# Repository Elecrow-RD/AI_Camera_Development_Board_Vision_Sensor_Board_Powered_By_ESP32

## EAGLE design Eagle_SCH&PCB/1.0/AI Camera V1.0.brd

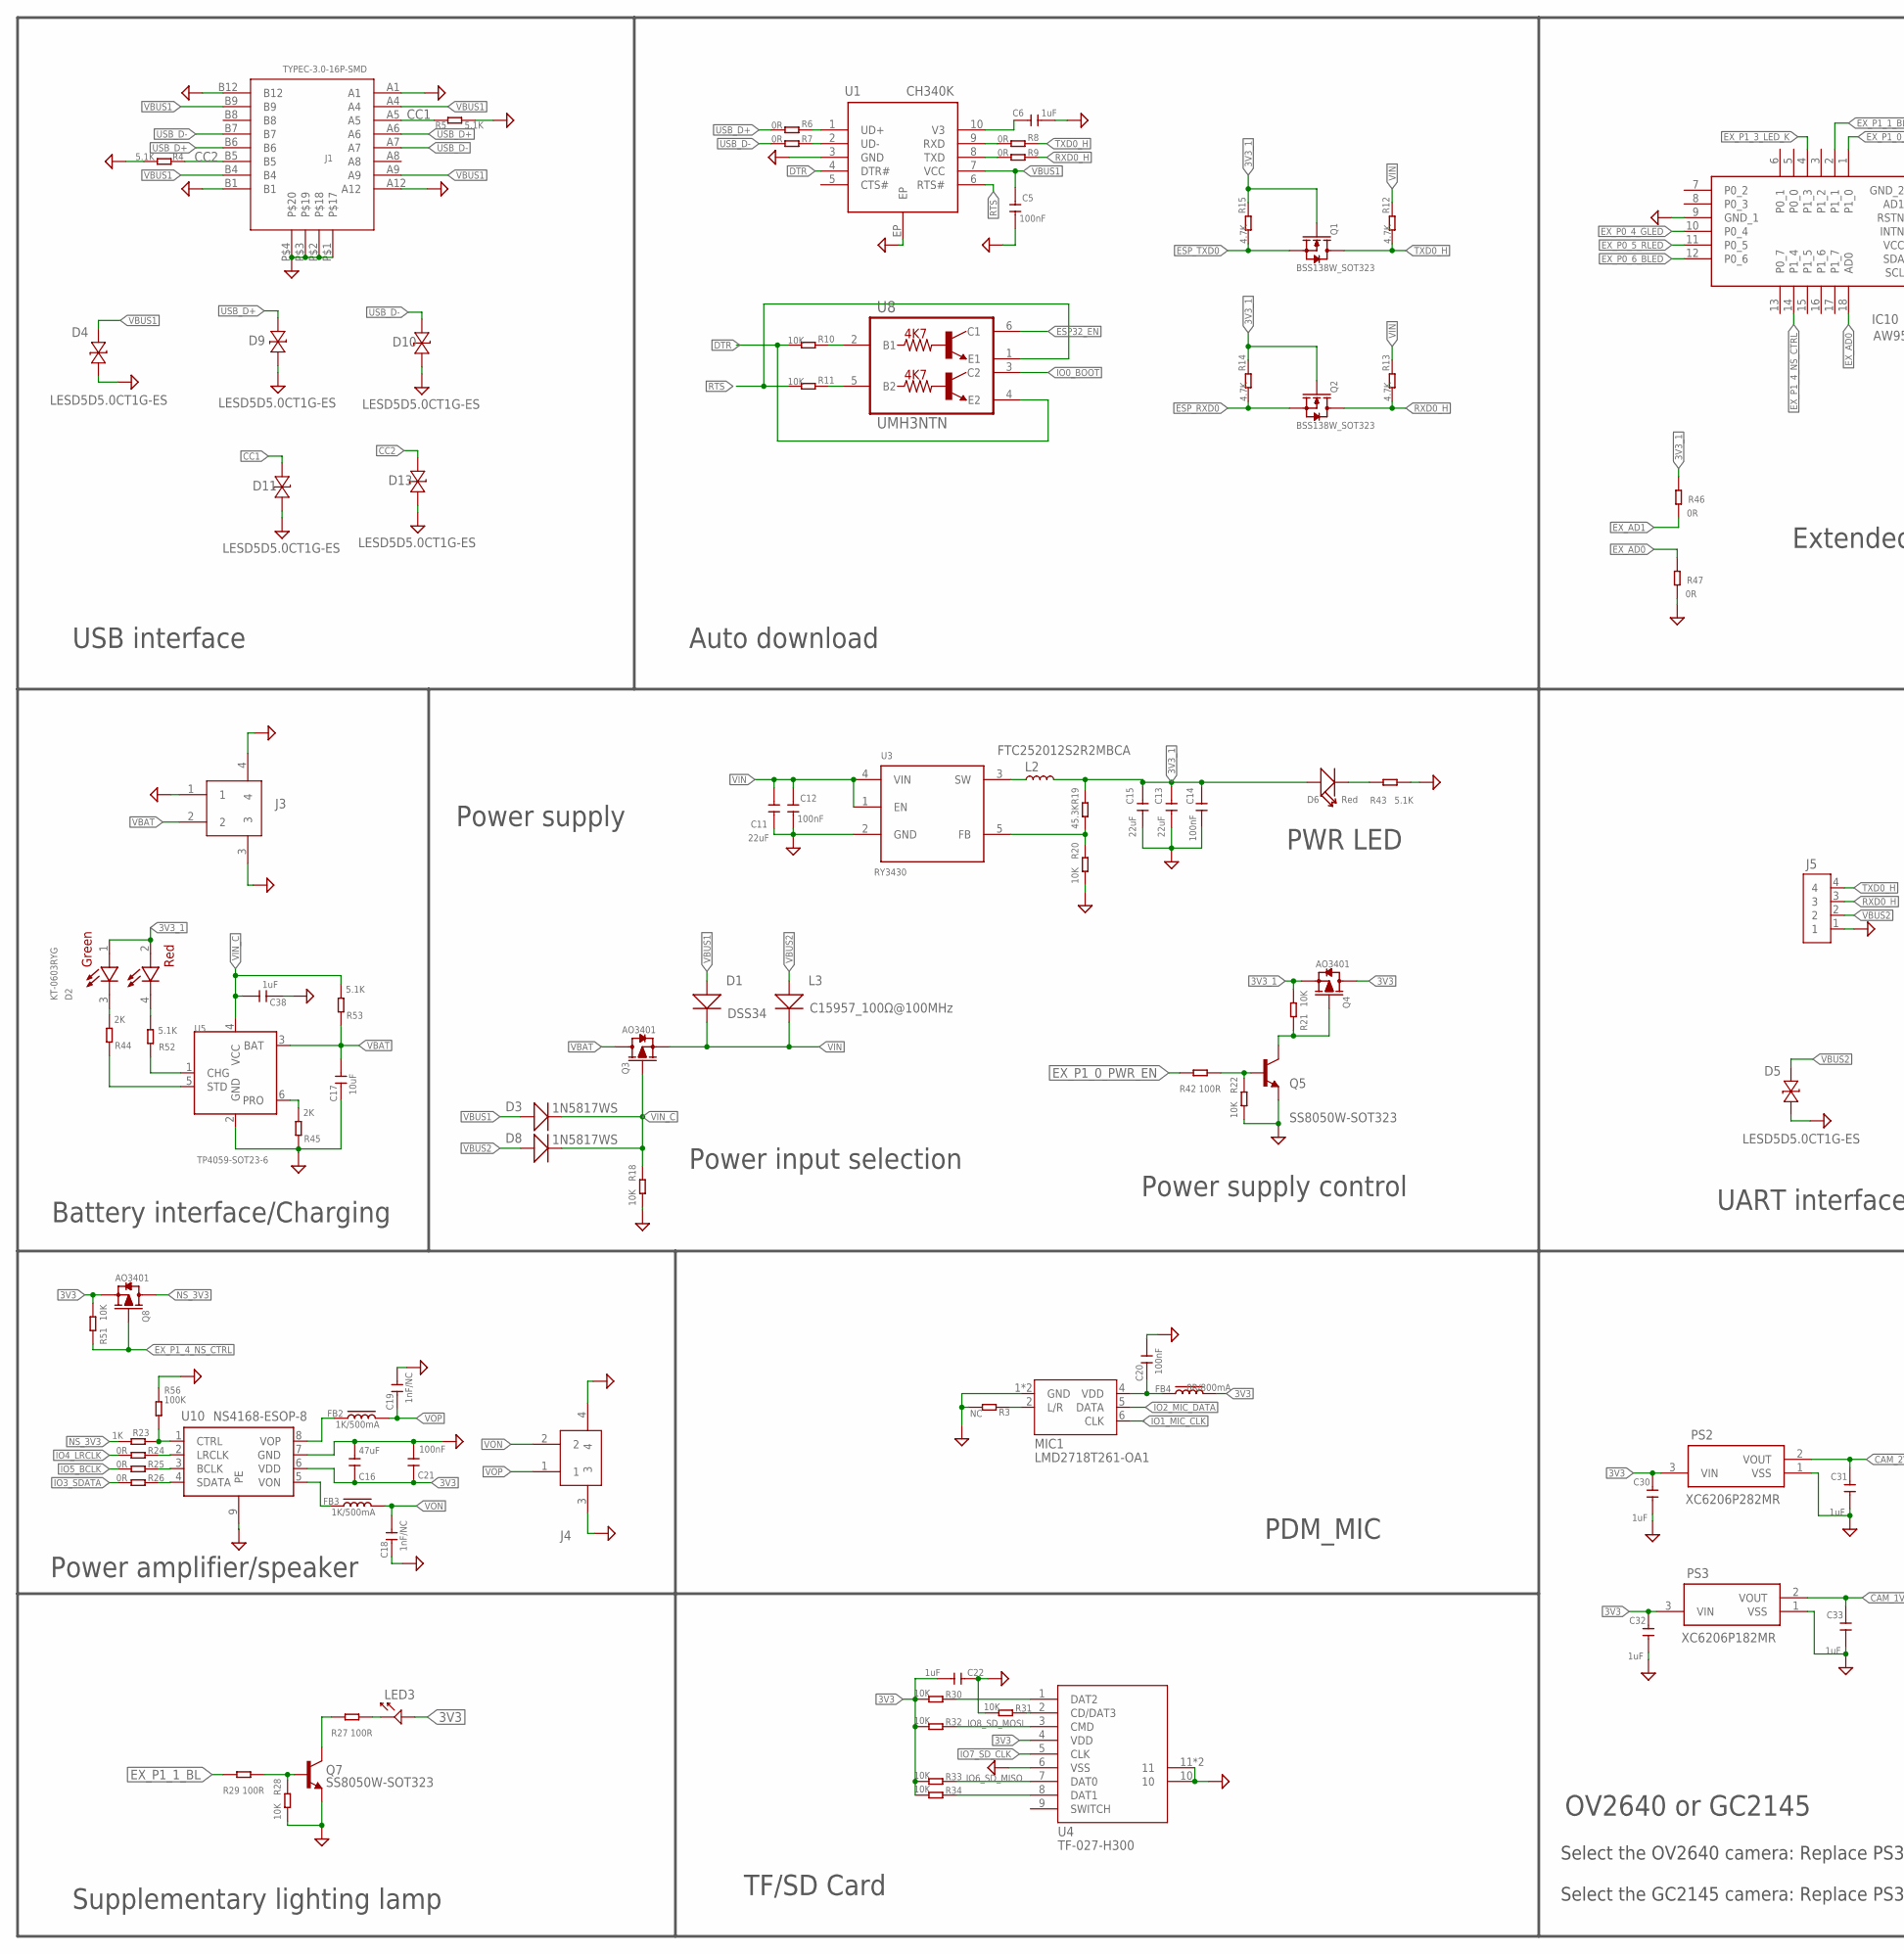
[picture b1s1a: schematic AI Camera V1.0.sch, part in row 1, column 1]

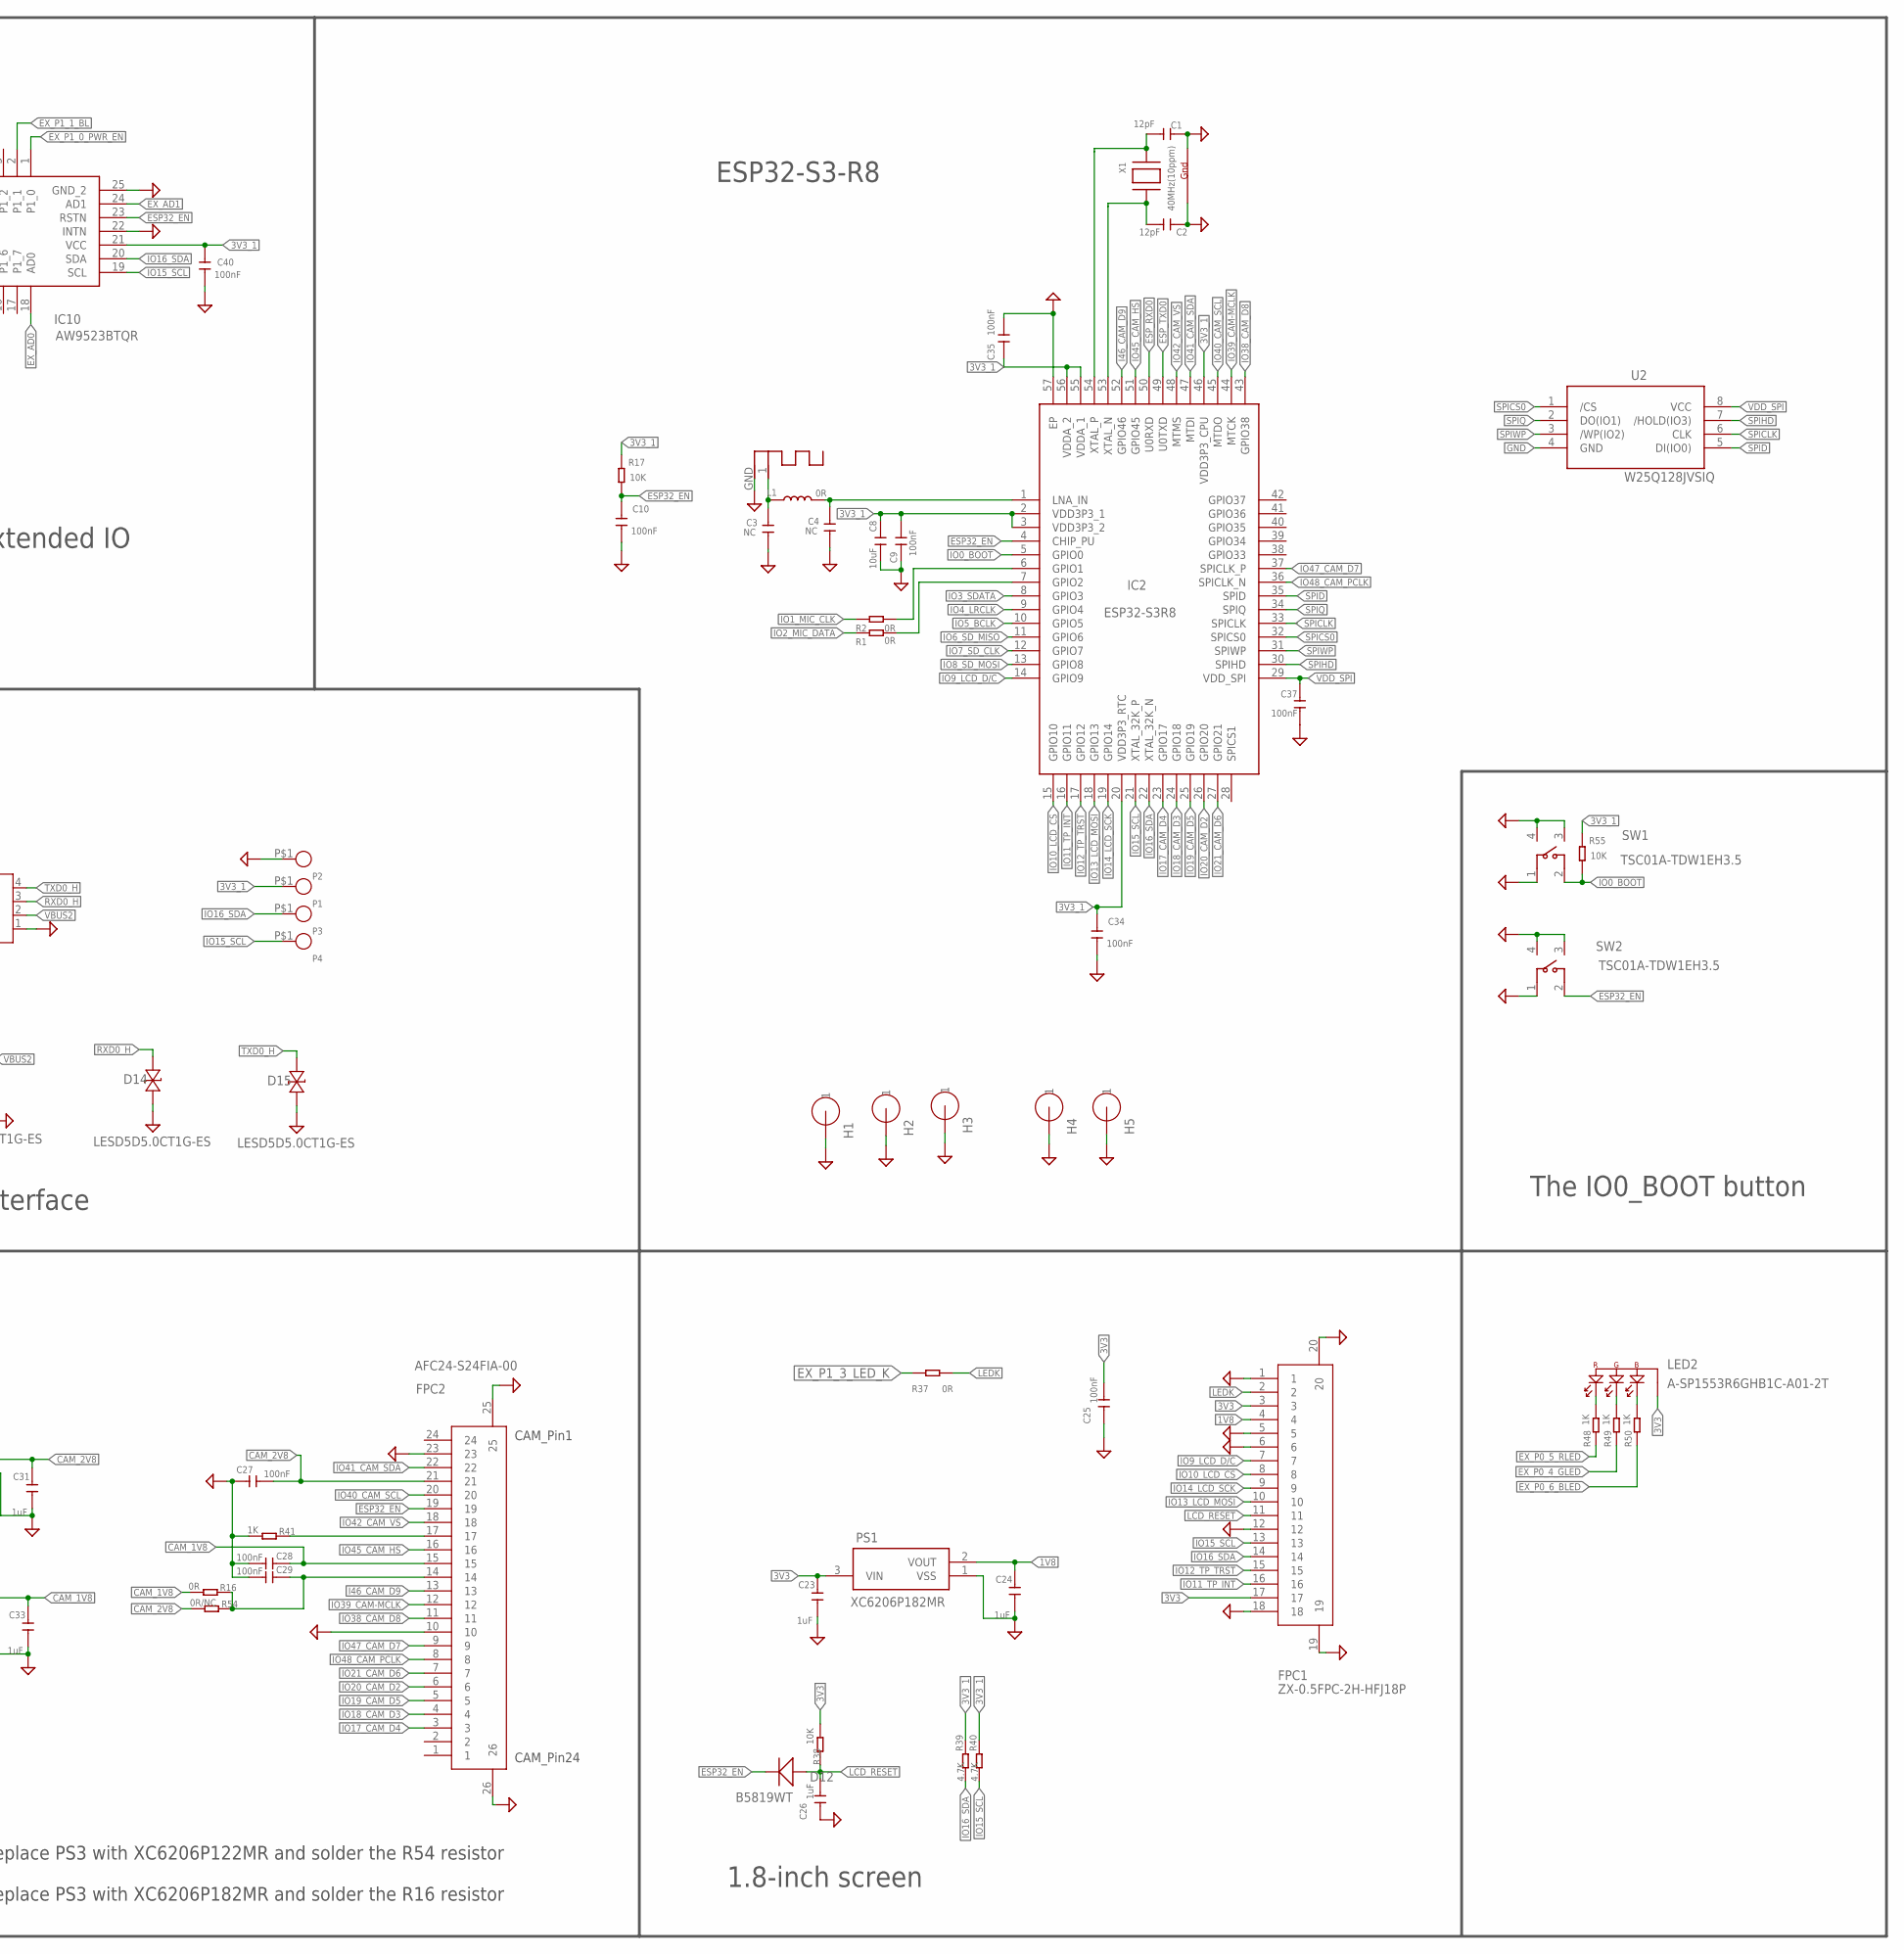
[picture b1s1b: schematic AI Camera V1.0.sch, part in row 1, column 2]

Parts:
ANT1: ADAFRUIT_ANTENNA; ADAFRUIT_RN-ANT
C1, C2: 12pF; C0402
C3, C4: NC; C0402
C5, C9, C10, C12, C14, C20, C21, C25, C27, C28, C29, C34, C35, C37, C40: 100nF; C0402
C6, C22, C23, C24, C26, C30, C31, C32, C33, C38: 1uF; C0402
C8, C17: 10uF; C0402
C11, C13, C15: 22uF; C0603
C16: 47uF; C0805
C18, C19: 1nF/NC; C0402
D1: DSS34; D_SOD123FL
D2: KT-0603RYG; LED_KT-0603RYG
D3, D8: 1N5817WS; D_SOD323
D4, D5, D9, D10, D11, D13, D14, D15: LESD5D5.0CT1G-ES; SOD-523_L1.2-W0.8-LS1.6-BI
D6: Red; LED0603
D12: B5819WT; D_SOD523
FB2, FB3: 1K/500mA; L0603
FB4: 0R/800mA; L0603
FPC1: ZX-0.5FPC-2H-HFJ18P; FPC-SMD_18P-P0.50_ZX-0.5FPC-2H-HFJ18P
FPC2: AFC24-S24FIA-00; FPC-SMD_P0.50-24P_QCHF-SM-H2.0
H1, H2, H3: HOLE; HOLE_M2
H4, H5: HOLE1; LONGSTRIPHOLE
IC2: ESP32-S3R8; QFN40P700X700X90-57N
IC10: AW9523BTQR; QFN50P400X400X80-25N
J1: TYPEC-3.0-16P-SMD; USB-3.0TYPEC-SMD
J3: ZX-SH1.0-2PLT1; CONN-SMD_2P-P1.00_XUNPU_WAFER-SH1.0-2PWB
J4: HC-1.25-2PWT; CONN-SMD_2P-P1.25-HC-1.25-2PWT
J5: HC-HY-4A-M; CONN-TH_4P-P2.00_HCTL_HC-HY-4A
L1: 0R; L0402
L2: FTC252012S2R2MBCA; IND-SMD_L2.5-W2.0_MHCHL2520
L3: C15957_100Ω@100MHz; D_SOD123FL
LED2: A-SP1553R6GHB1C-A01-2T; LED-SMD_4P-L3.2-W2.7-BL_A-SP1553R6GHB1C-A01-2T
LED3: 3014_LED; LED_3014_SMT
MIC1: LMD2718T261-OA1; MIC-SMD_6P-L2.8-W1.9-P0.98-TL
P1, P2, P3, P4: TEST_PADPAD-1.5MM; TEST_PAD-1.5MM
PS1, PS3: XC6206P182MR; SOT95P280X130-3N
PS2: XC6206P282MR; SOT95P280X130-3N
Q1, Q2: BSS138W_SOT323; MOS_SOT323
Q3, Q4, Q8: AO3401; PMOS_SOT23
Q5, Q7: SS8050W-SOT323; MOS_SOT323
R1, R2, R6, R7, R8, R9, R16, R24, R25, R26, R37, R46, R47: 0R; R0402
R3: NC; R0402
R4, R5, R43, R52, R53: 5.1K; R0402
R10, R11, R17, R18, R20, R21, R22, R28, R30, R31, R32, R33, R34, R38, R51, R55: 10K; R0402
R12, R13, R14, R15, R39, R40: 4.7K; R0402
R19: 45.3K; R0402
R23, R41, R48, R49, R50: 1K; R0402
R27, R29, R42: 100R; R0402
R44, R45: 2K; R0402
R54: 0R/NC; R0402
R56: 100K; R0402
SW1, SW2: TSC01A-TDW1EH3.5; KEY-SMD_4P-L4.6-W2.4_TSC01A-TDW1FH3.5
U1: CH340K; ESOP-10-EP-150MIL
U2: W25Q128JVSIQ; CKP_W25QXX-SOP-8-208MIL
U3: RY3430; IC_SOT23-5
U4: TF-027-H300; TF-SMD_HYCW104-TF08-375B
U5: TP4059-SOT23-6; SOT23-6L
U8: UMH3NTN; SOP65P210X100-6N
U10: NS4168-ESOP-8
X1: 40MHz(10ppm); ADAFRUIT_NX3225

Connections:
1V8: C24.1, FPC1.4, PS1.2 (VOUT)
3V3: C16.1, C21.1, C22.2, C23.1, C25.2, C30.1, C32.1, FB4.2, FPC1.3, FPC1.17, LED2.3 (GND), LED3.1, PS1.3 (VIN), PS2.3 (VIN), PS3.3 (VIN), Q4.3 (D), Q8.2 (S), R30.2, R32.2, R33.2, R34.2, R38.2, R51.2, U4.4 (VDD), U10.6 (VDD)
3V3_1: C8.1, C9.2, C13.2, C14.1, C15.2, C34.2, C35.1, C40.2, D2.1, D2.2, D6.+, IC2.2 (VDD3P3_1), IC2.3 (VDD3P3_2), IC2.20 (VDD3P3_RTC), IC2.46 (VDD3P3_CPU), IC2.55 (VDDA_1), IC2.56 (VDDA_2), IC10.21 (VCC), L2.2, P1.P$1, Q1.1 (G), Q2.1 (G), Q4.2 (S), R14.1, R15.1, R17.1, R19.1, R21.2, R39.1, R40.1, R46.1, R55.1
CAM_1V8: C28.1, C33.1, FPC2.15, PS3.2 (VOUT), R16.2
CAM_2V8: C27.1, C31.1, FPC2.21, PS2.2 (VOUT), R54.2
CC1: D11.2, J1.A5, R5.1
CC2: D13.2, J1.B5, R4.1
DOVDD: C29.1, FPC2.14, R16.1, R54.1
DTR: R10.2, U1.4 (DTR#), U8.4 (E2)
ESP32_EN: C10.2, D12.-, FPC2.19, IC2.4 (CHIP_PU), IC10.23 (RSTN), R17.2, SW2.2, U8.6 (C1)
ESP_RXD0: IC2.50 (U0RXD), Q2.2 (S), R14.2
ESP_TXD0: IC2.49 (U0TXD), Q1.2 (S), R15.2
EX_AD0: IC10.18 (AD0), R47.1
EX_AD1: IC10.24 (AD1), R46.2
EX_P0_4_GLED: IC10.10 (P0_4), R49.1
EX_P0_5_RLED: IC10.11 (P0_5), R48.1
EX_P0_6_BLED: IC10.12 (P0_6), R50.1
EX_P1_0_PWR_EN: IC10.1 (P1_0), R42.1
EX_P1_1_BL: IC10.2 (P1_1), R29.1
EX_P1_3_LED_K: IC10.4 (P1_3), R37.1
EX_P1_4_NS_CTRL: IC10.14 (P1_4), Q8.1 (G), R51.1
GND: ANT1.GND, C1.1, C2.1, C3.2, C4.2, C5.2, C6.2, C8.2, C9.1, C10.1, C11.1, C12.2, C13.1, C14.2, C15.1, C16.2, C17.1, C18.1, C19.2, C20.2, C21.2, C22.1, C23.2, C24.2, C25.1, C26.1, C27.2, C28.2, C29.2, C30.2, C31.2, C32.2, C33.2, C34.1, C35.2, C37.1, C38.1, C40.1, D4.1, D5.1, D9.1, D10.1, D11.1, D13.1, D14.1, D15.1, FPC1.1, FPC1.5, FPC1.6, FPC1.12, FPC1.18, FPC1.19, FPC1.20, FPC2.10, FPC2.23, FPC2.25, FPC2.26, H1.1, H2.1, H3.1, H4.1, H4.2, H5.1, H5.2, IC2.57 (EP), IC10.9 (GND_1), IC10.22 (INTN), IC10.25 (GND_2), J1.A1, J1.A12, J1.B1, J1.B12, J1.P$1, J1.P$2, J1.P$3, J1.P$4, J3.1, J3.3, J3.4, J4.3, J4.4, J5.1, MIC1.1 (GND), MIC1.3 (GND), P2.P$1, PS1.1 (VSS), PS2.1 (VSS), PS3.1 (VSS), Q5.2 (E), Q7.2 (E), R3.2, R4.2, R5.2, R18.2, R20.2, R22.2, R28.2, R31.2, R41.2, R43.2, R45.1, R47.2, R56.1, SW1.1, SW1.3, SW1.4, SW2.1, SW2.3, SW2.4, U1.3 (GND), U1.EP, U2.4 (GND), U3.2 (GND), U4.6 (VSS), U4.10, U4.11, U4.12 (11), U5.2 (GND), U10.7 (GND), U10.9 (PE), X1.2 (G2), X1.4 (G1)
I46_CAM_D9: FPC2.13, IC2.52 (GPIO46)
IO0_BOOT: IC2.5 (GPIO0), R55.2, SW1.2, U8.3 (C2)
IO1_MIC_CLK: MIC1.6 (CLK), R1.1
IO2_MIC_DATA: MIC1.5 (DATA), R2.1
IO3_SDATA: IC2.8 (GPIO3), R26.2
IO4_LRCLK: IC2.9 (GPIO4), R24.2
IO5_BCLK: IC2.10 (GPIO5), R25.2
IO6_SD_MISO: IC2.11 (GPIO6), R33.1, U4.7 (DAT0)
IO7_SD_CLK: IC2.12 (GPIO7), U4.5 (CLK)
IO8_SD_MOSI: IC2.13 (GPIO8), R32.1, U4.3 (CMD)
IO9_LCD_D/C: FPC1.7, IC2.14 (GPIO9)
IO10_LCD_CS: FPC1.8, IC2.15 (GPIO10)
IO11_TP_INT: FPC1.16, IC2.16 (GPIO11)
IO12_TP_TRST: FPC1.15, IC2.17 (GPIO12)
IO13_LCD_MOSI: FPC1.10, IC2.18 (GPIO13)
IO14_LCD_SCK: FPC1.9, IC2.19 (GPIO14)
IO15_SCL: FPC1.13, IC2.21 (XTAL_32K_P), IC10.19 (SCL), P4.P$1, R40.2
IO16_SDA: FPC1.14, IC2.22 (XTAL_32K_N), IC10.20 (SDA), P3.P$1, R39.2
IO17_CAM_D4: FPC2.3, IC2.23 (GPIO17)
IO18_CAM_D3: FPC2.4, IC2.24 (GPIO18)
IO19_CAM_D5: FPC2.5, IC2.25 (GPIO19)
IO20_CAM_D2: FPC2.6, IC2.26 (GPIO20)
IO21_CAM_D6: FPC2.7, IC2.27 (GPIO21)
IO38_CAM_D8: FPC2.11, IC2.43 (GPIO38)
IO39_CAM-MCLK: FPC2.12, IC2.44 (MTCK)
IO40_CAM_SCL: FPC2.20, IC2.45 (MTDO)
IO41_CAM_SDA: FPC2.22, IC2.47 (MTDI)
IO42_CAM_VS: FPC2.18, IC2.48 (MTMS)
IO45_CAM_HS: FPC2.16, IC2.51 (GPIO45)
IO47_CAM_D7: FPC2.9, IC2.37 (SPICLK_P)
IO48_CAM_PCLK: FPC2.8, IC2.36 (SPICLK_N)
LCD_RESET: C26.2, D12.+, FPC1.11, R38.1
LEDK: FPC1.2, R37.2
unnamed: IC2.6 (GPIO1), R1.2
unnamed: R31.1, U4.2 (CD/DAT3)
unnamed: MIC1.2 (L/R), R3.1
unnamed: ANT1.1 (FEED), C3.1, L1.1
unnamed: C4.1, IC2.1 (LNA_IN), L1.2
unnamed: D6.-, R43.1
unnamed: D2.4, R52.2
unnamed: R7.1, U1.2 (UD-)
unnamed: R6.1, U1.1 (UD+)
unnamed: R8.2, U1.9 (RXD)
unnamed: R9.2, U1.8 (TXD)
unnamed: R10.1, U8.2 (B1)
unnamed: R11.1, U8.5 (B2)
unnamed: C6.1, U1.10 (V3)
unnamed: IC2.7 (GPIO2), R2.2
unnamed: R52.1, U5.1 (CHG)
unnamed: L2.1, U3.3 (SW)
unnamed: C2.2, IC2.53 (XTAL_N), X1.3 (X2)
unnamed: R19.2, R20.1, U3.5 (FB)
unnamed: R24.1, U10.2 (LRCLK)
unnamed: R25.1, U10.3 (BCLK)
unnamed: R26.1, U10.4 (SDATA)
unnamed: Q4.1 (G), Q5.3 (C), R21.1
unnamed: Q5.1 (B), R22.1, R42.2
unnamed: R45.2, U5.6 (PRO)
unnamed: FB3.1, U10.5 (VON)
unnamed: FB2.1, U10.8 (VOP)
unnamed: C20.1, FB4.1, MIC1.4 (VDD)
unnamed: LED3.2, R27.2
unnamed: Q7.3 (C), R27.1
unnamed: Q7.1 (B), R28.1, R29.2
unnamed: LED2.2 (R), R48.2
unnamed: R30.1, U4.1 (DAT2)
unnamed: C1.2, IC2.54 (XTAL_P), X1.1 (X1)
unnamed: FPC2.17, R41.1
unnamed: LED2.1 (G), R49.2
unnamed: LED2.4 (B), R50.2
unnamed: R34.1, U4.8 (DAT1)
unnamed: D2.3, R44.2
unnamed: R44.1, U5.5 (STD)
NS_3V3: Q8.3 (D), R23.2
NS_CTRL: R23.1, R56.2, U10.1 (CTRL)
RTS: R11.2, U1.6 (RTS#), U8.1 (E1)
RXD0_H: D14.2, J5.3, Q2.3 (D), R9.1, R13.2
SPICLK: IC2.33 (SPICLK), U2.6 (CLK)
SPICS0: IC2.32 (SPICS0), U2.1 (/CS)
SPID: IC2.35 (SPID), U2.5 (DI(IO0))
SPIHD: IC2.30 (SPIHD), U2.7 (/HOLD(IO3))
SPIQ: IC2.34 (SPIQ), U2.2 (DO(IO1))
SPIWP: IC2.31 (SPIWP), U2.3 (/WP(IO2))
TXD0_H: D15.2, J5.4, Q1.3 (D), R8.1, R12.2
USB_D+: D9.2, J1.A6, J1.B6, R6.2
USB_D-: D10.2, J1.A7, J1.B7, R7.2
VBAT: C17.2, J3.2, Q3.3 (D), R53.1, U5.3 (BAT)
VBUS1: C5.1, D1.+, D3.+, D4.2, J1.A4, J1.A9, J1.B4, J1.B9, U1.7 (VCC)
VBUS2: D5.2, D8.+, J5.2, L3.+
VDD_SPI: C37.2, IC2.29 (VDD_SPI), U2.8 (VCC)
VIN: C11.2, C12.1, D1.-, L3.-, Q3.2 (S), R12.1, R13.1, U3.1 (EN), U3.4 (VIN)
VIN_C: C38.2, D3.-, D8.-, Q3.1 (G), R18.1, R53.2, U5.4 (VCC)
VON: C18.2, FB3.2, J4.2
VOP: C19.1, FB2.2, J4.1

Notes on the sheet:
USB interface
Auto download
ESP32-S3-R8
The IO0_BOOT button
UART interface
Power supply
Power input selection
Power supply control
Battery interface/Charging
Power amplifier/speaker
Supplementary lighting lamp
TF/SD Card
OV2640 or GC2145
1.8-inch screen
PDM_MIC
PWR LED
Extended IO
Select the OV2640 camera: Replace PS3 with XC6206P122MR and solder the R54 resistor Select the GC2145 camera: Replace PS3 with XC6206P182MR and solder the R16 resistor
CAM_Pin1
CAM_Pin24

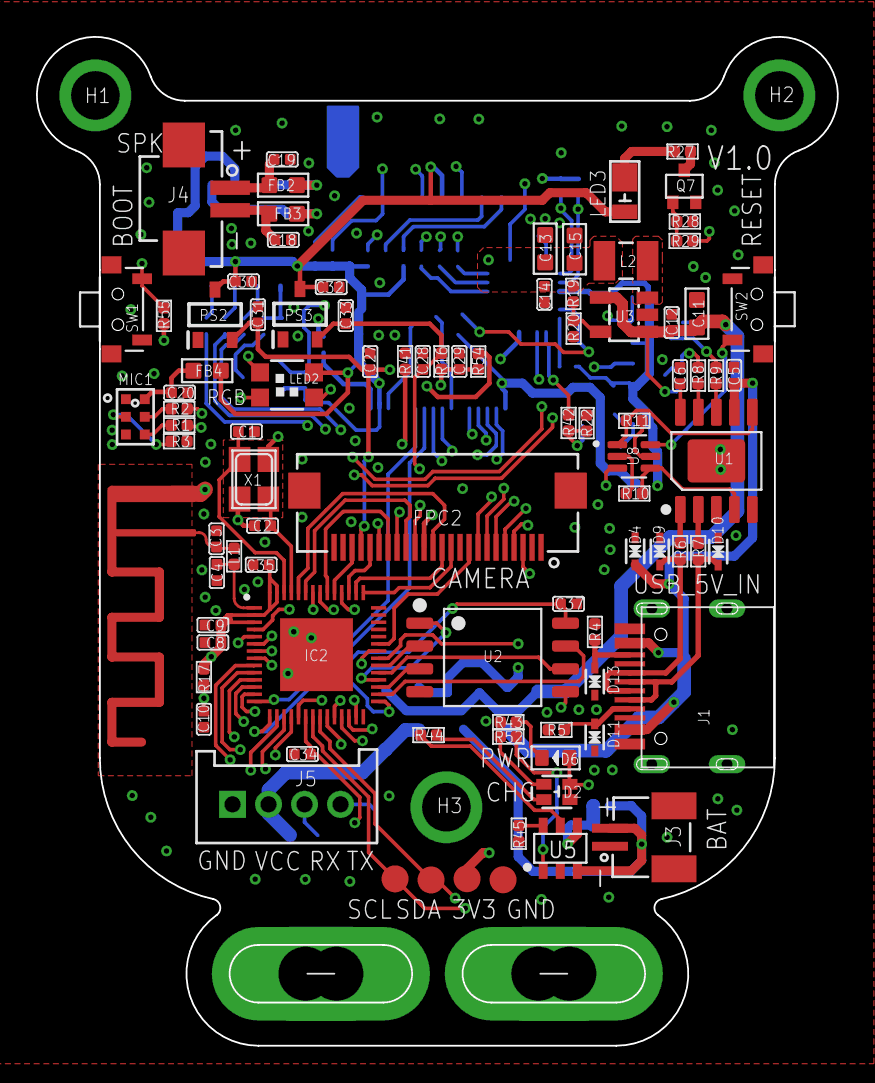
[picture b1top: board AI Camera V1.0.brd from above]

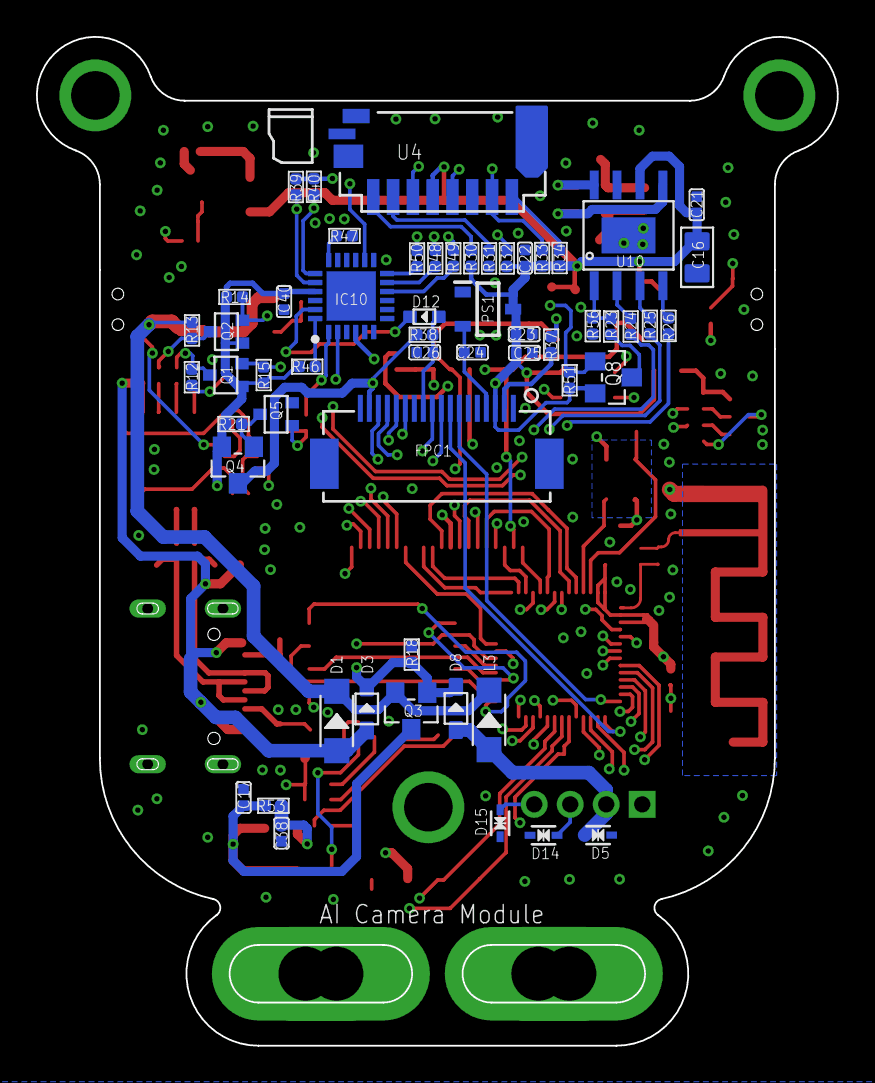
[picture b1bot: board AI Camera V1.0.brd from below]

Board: 4 copper layers, 44.5 x 56.0 mm, 152 parts (56 on the bottom side), 116 nets.

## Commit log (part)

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2026-04-08 Clean history: remove all secrets
